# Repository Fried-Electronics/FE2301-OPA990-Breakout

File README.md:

Breakout board for OPA990 operational amplifier, or other SOT23-5 amplifiers

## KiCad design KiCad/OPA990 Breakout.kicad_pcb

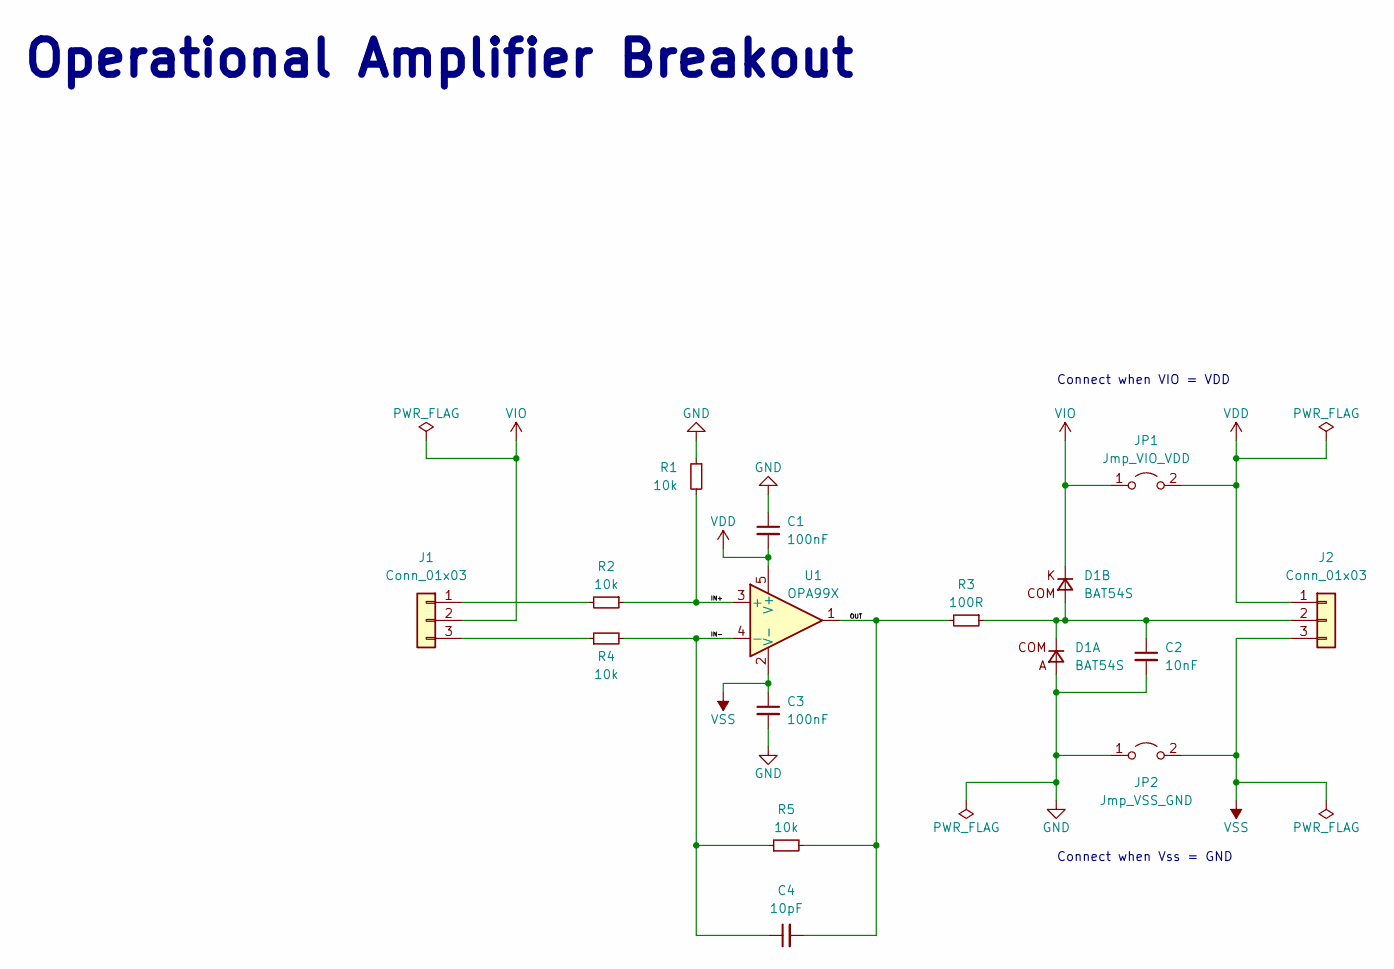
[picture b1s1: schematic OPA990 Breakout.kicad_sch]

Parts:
C1, C3: 100nF; C_0603_1608Metric; Manufacturer Part Number 885012206095; Mouser Part Number 710-885012206095
C2: 10nF; C_0603_1608Metric; Manufacturer Part Number CL10B103KB8NNNL; Mouser Part Number 187-CL10B103KB8NNNL
C4: 10pF; C_0603_1608Metric; Manufacturer Part Number VJ0603A100GXACW1BC; Mouser Part Number 77-VJ0603A100GXACBC
D1: BAT54S; SOT-23-3; Manufacturer Part Number BAT54S-7-F; Mouser Part Number 621-BAT54S-F
J1, J2: Conn_01x03; PinHeader_1x03_P2.54mm_Vertical; Manufacturer Part Number 22-28-4030; Mouser Part Number 538-22-28-4030
JP1: Jmp_VIO_VDD; SolderJumper-2_P1.3mm_Open_TrianglePad1.0x1.5mm
JP2: Jmp_VSS_GND; SolderJumper-2_P1.3mm_Open_TrianglePad1.0x1.5mm
R1, R2, R4, R5: 10k; R_0603_1608Metric; Manufacturer Part Number RN73R1JTTD1002B25; Mouser Part Number 660-RN73R1JTD1002B25
R3: 100R; R_0603_1608Metric; Manufacturer Part Number RN73R1JTTD1000B25; Mouser Part Number 660-RN73R1JTD1000B25
U1: OPA99X; SOT-23-5; Mouser Part Number 595-OPA992IDBVR

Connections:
/IN+: R1.2, R2.1, U1.3 (+)
/IN-: C4.1, R4.2, R5.1, U1.4 (-)
/OUT: C4.2, R3.2, R5.2, U1.1
GND: C1.1, C2.2, C3.2, D1.1 (A), JP2.1 (A), R1.1
unnamed: C2.1, D1.3 (COM), J2.2, R3.1
unnamed: J1.1, R2.2
unnamed: J1.3, R4.1
VDD: C1.2, J2.1, JP1.2 (B), U1.5 (V+)
VIO: D1.2 (K), J1.2, JP1.1 (A)
VSS: C3.1, J2.3, JP2.2 (B), U1.2 (V-)

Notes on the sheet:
Connect when VIO = VDD
Connect when Vss = GND
Operational Amplifier Breakout

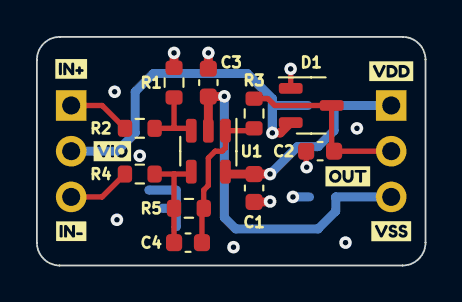
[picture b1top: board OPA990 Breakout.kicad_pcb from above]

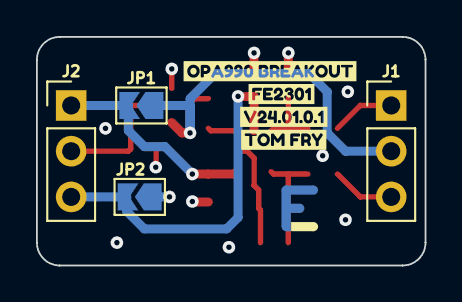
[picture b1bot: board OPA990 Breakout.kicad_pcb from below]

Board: 4 copper layers, 21.6 x 12.7 mm, 25 parts (8 on the bottom side), 10 nets.

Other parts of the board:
kibuzzard-659D8DDF: G***; kibuzzard-659D8DDF
kibuzzard-659D8E26: G***; kibuzzard-659D8E26
kibuzzard-659D8E62: G***; kibuzzard-659D8E62
kibuzzard-659D8E71: G***; kibuzzard-659D8E71
kibuzzard-659D9D0E: G***; kibuzzard-659D9D0E
kibuzzard-659D9D4E: G***; kibuzzard-659D9D4E
kibuzzard-659D9D29: G***; kibuzzard-659D9D29
kibuzzard-659D9D38: G***; kibuzzard-659D9D38
kibuzzard-659D9D68: G***; kibuzzard-659D9D68
kibuzzard-659D9D77: G***; kibuzzard-659D9D77

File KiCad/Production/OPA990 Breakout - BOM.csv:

"Source:","C:\Users\tomfr\Documents\GitHub\FE2301-OPA990-Breakout\KiCad\OPA990 Breakout.kicad_sch"
"Date:","09/01/2024 18:47:58"
"Tool:","Eeschema 7.0.9"
"Generator:","C:\Program Files\KiCad\7.0\bin\scripting\plugins/bom_csv_grouped_by_value.py"
"Component Count:","13"

"Collated Components:"

"Item","Qty","Reference(s)","Value","LibPart","Footprint","Datasheet","DNP","Manufacturer Part Number","Mouser Part Number"
"1","2","C1, C3","100nF","Device:C_Small","Capacitor_SMD:C_0603_1608Metric","~","","885012206095","710-885012206095"
"2","1","C2","10nF","Device:C_Small","Capacitor_SMD:C_0603_1608Metric","~","","CL10B103KB8NNNL","187-CL10B103KB8NNNL"
"3","1","C4","10pF","Device:C_Small","Capacitor_SMD:C_0603_1608Metric","~","","VJ0603A100GXACW1BC","77-VJ0603A100GXACBC"
"4","1","D1","BAT54S",":BAT54S_1","Package_TO_SOT_SMD:SOT-23-3","~","","BAT54S-7-F","621-BAT54S-F"
"5","2","J1, J2","Conn_01x03","Connector_Generic:Conn_01x03","Connector_PinHeader_2.54mm:PinHeader_1x03_P2.54mm_Vertical","~","","22-28-4030","538-22-28-4030"
"6","4","R1, R2, R4, R5","10k","Device:R_Small","Resistor_SMD:R_0603_1608Metric","~","","RN73R1JTTD1002B25","660-RN73R1JTD1002B25"
"7","1","R3","100R","Device:R_Small","Resistor_SMD:R_0603_1608Metric","~","","RN73R1JTTD1000B25","660-RN73R1JTD1000B25"
"8","1","U1","OPA99X","friedElectronicsSymbols:OPA99X","Package_TO_SOT_SMD:SOT-23-5","","","OPA992IDBVR","595-OPA992IDBVR"

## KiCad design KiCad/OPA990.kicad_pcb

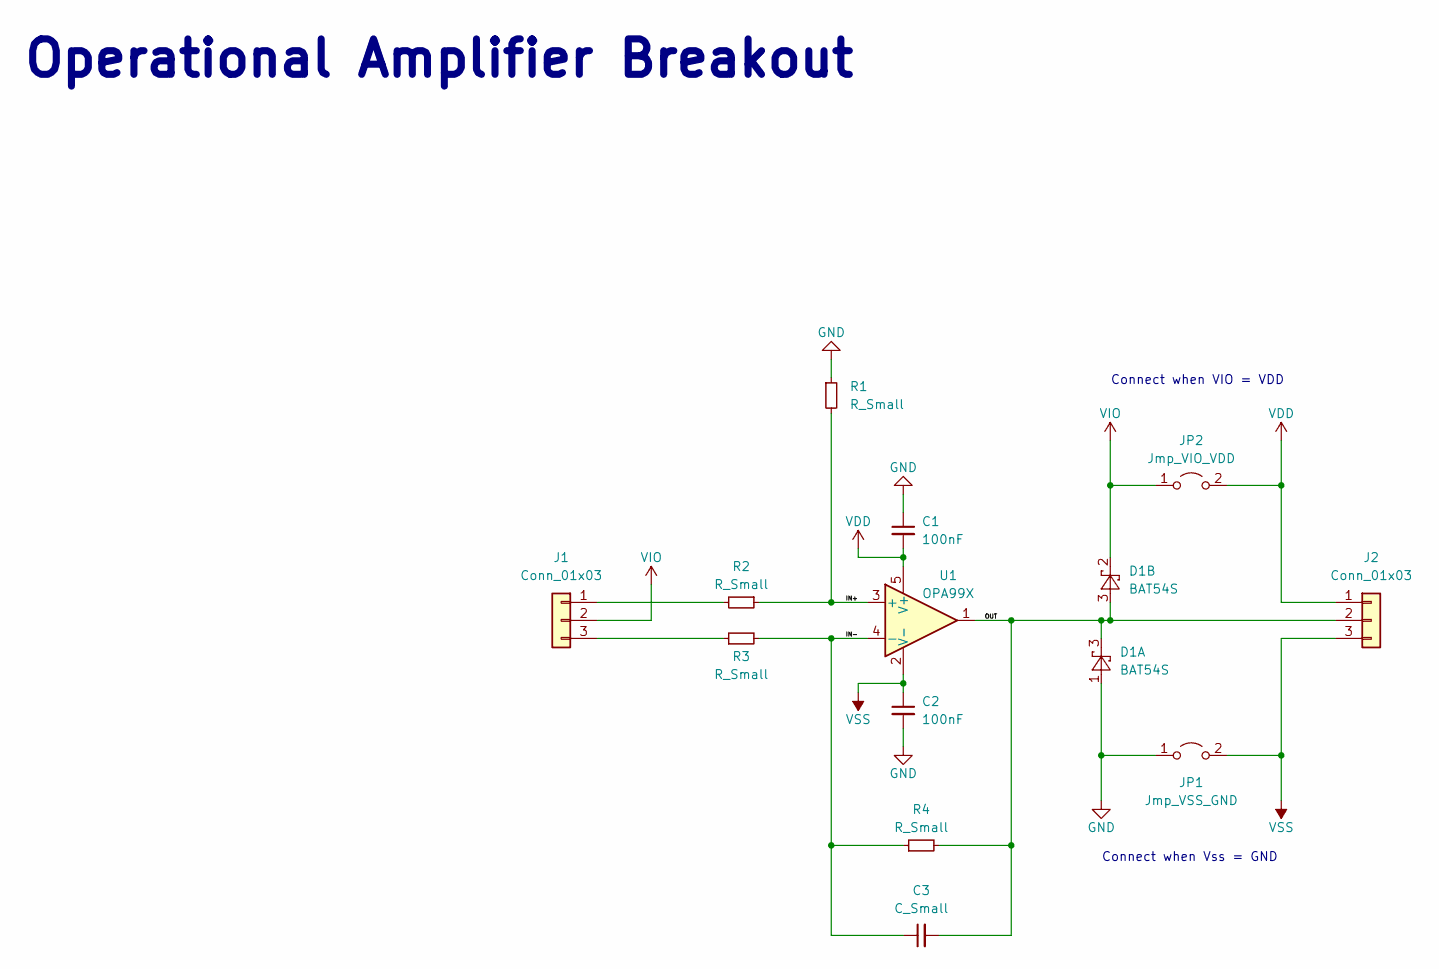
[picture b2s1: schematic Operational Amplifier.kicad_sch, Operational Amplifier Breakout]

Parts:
C1, C2: 100nF; C_0603_1608Metric
C3: C_Small; C_0603_1608Metric
D1: BAT54S; SOT-23
J1, J2: Conn_01x03; PinHeader_1x03_P2.54mm_Vertical
JP1: Jmp_VSS_GND; SolderJumper-2_P1.3mm_Open_TrianglePad1.0x1.5mm
JP2: Jmp_VIO_VDD; SolderJumper-2_P1.3mm_Open_TrianglePad1.0x1.5mm
R1, R2, R3, R4: R_Small; R_0603_1608Metric
U1: OPA99X; SOT-23-5

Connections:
/IN+: R1.2, R2.1, U1.3 (+)
/IN-: C3.1, R3.2, R4.1, U1.4 (-)
/OUT: C3.2, D1.3, J2.2, R4.2, U1.1
GND: C1.1, C2.2, D1.1, JP1.1 (A), R1.1
unnamed: J1.1, R2.2
unnamed: J1.3, R3.1
VDD: C1.2, J2.1, JP2.2 (B), U1.5 (V+)
VIO: D1.2, J1.2, JP2.1 (A)
VSS: C2.1, J2.3, JP1.2 (B), U1.2 (V-)

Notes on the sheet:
Connect when VIO = VDD
Connect when Vss = GND
Operational Amplifier Breakout

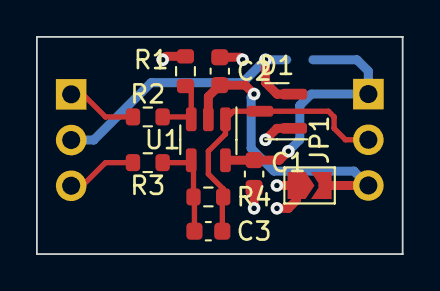
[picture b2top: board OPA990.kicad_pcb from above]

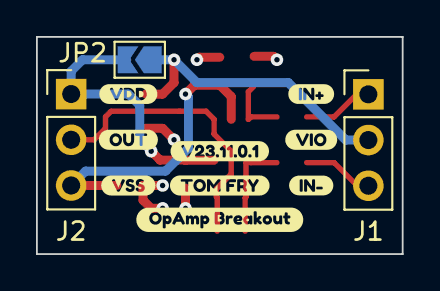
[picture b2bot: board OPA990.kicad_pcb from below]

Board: 4 copper layers, 20.3 x 12.1 mm, 22 parts (12 on the bottom side), 9 nets.

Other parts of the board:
kibuzzard-655015A2: G***; kibuzzard-655015A2
kibuzzard-655015B1: G***; kibuzzard-655015B1
kibuzzard-655015F1: G***; kibuzzard-655015F1
kibuzzard-6550156A: G***; kibuzzard-6550156A
kibuzzard-6550157F: G***; kibuzzard-6550157F
kibuzzard-6550158B: G***; kibuzzard-6550158B
kibuzzard-65501596: G***; kibuzzard-65501596
kibuzzard-65501606: G***; kibuzzard-65501606
kibuzzard-65501622: G***; kibuzzard-65501622

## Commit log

2023-11-12 updated kicad
2023-12-21 added datasheets
2024-01-08 Changed KiCad name to OPA990
2024-01-09 renamed files
2024-01-09 updated kicad files
2024-01-09 removed pcb lock
